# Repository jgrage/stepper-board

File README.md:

# stepper-board
Stepper motor controller board with NEMA-23 dimensions. This board was designed with KiCad. All manufacturing files are prepared for production at [JLCPCB](https://jlcpcb.com/). The surface mount components are placed on the top layer. All through-hole connectors are placed on the bottom layer. 

## Driver
The board features a socket for a Pololu [A4988 breakout board](https://www.pololu.com/product/1182). This chip can drive stepper motors with up to 2A per coil. Make sure to connect an appropriate power supply to the barrel jack.

## Controller
The firmware resides in an Arduino Nano that will plug into the 30-pin socket. Make sure to use a board with FT232RL chip so your controller will have a unique USB ID. The cheaper CH340 chips that are used on many clones all share the same ID. The controller receives serial commands and its 5V power via the Mini USB connector. 

## Limit switches
The firmware currently supports two mechanical limit switches in a normally closed configuration. Connect these to the two leftmost/rightmost pins of the 6-pin connector. The two middle pins are reserved for a mechanical reference switch, but this feature is not yet implemented in the firmware.

# Top layer

# Bottom layer

# Assembled

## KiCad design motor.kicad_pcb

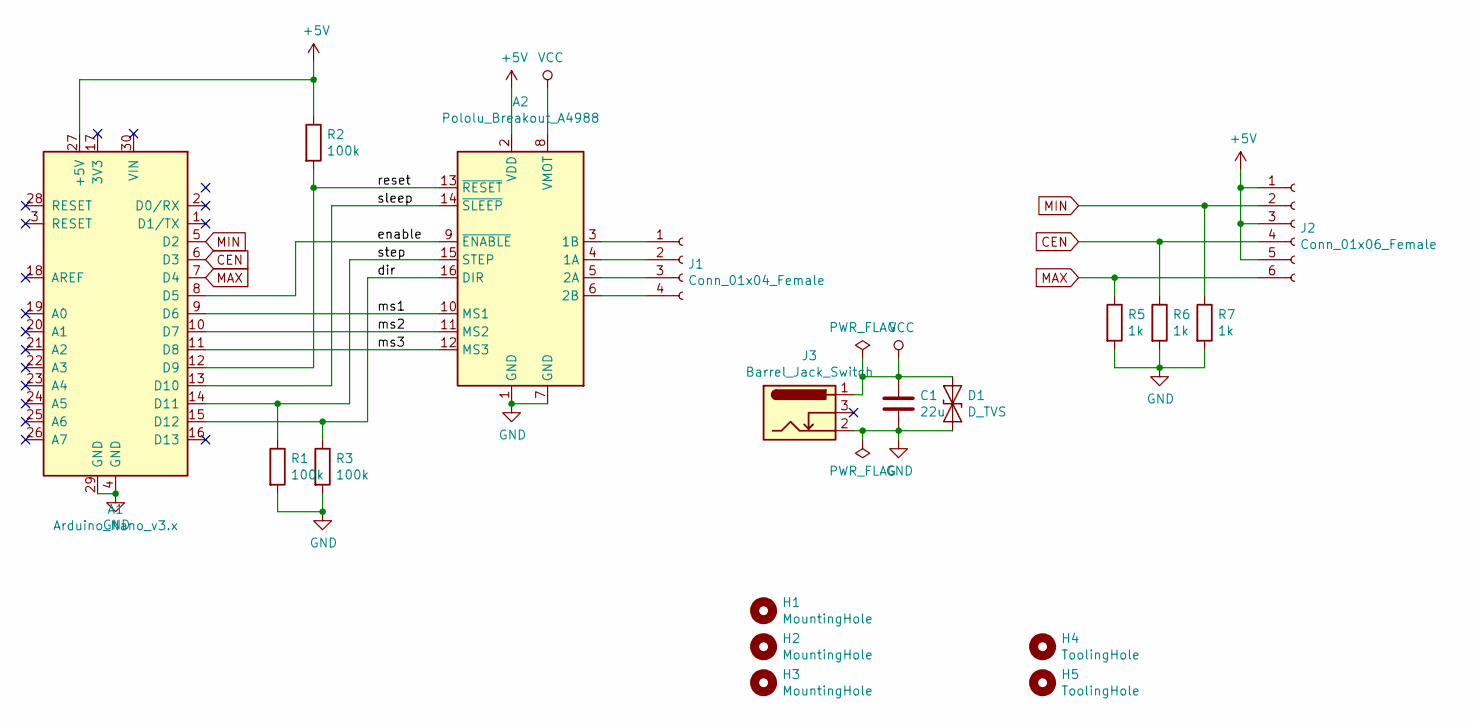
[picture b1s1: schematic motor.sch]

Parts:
A1: Arduino_Nano_v3.x; Arduino_Nano
A2: Pololu_Breakout_A4988; Pololu_Breakout-16_15.2x20.3mm
C1: 22u; C_1206_3216Metric; LCSC C13585
D1: D_TVS; D_SMB; LCSC C284012
H1, H2, H3: MountingHole; MountingHole_5mm
H4, H5: ToolingHole; Tooling_Hole_JLCPCB
J1: Conn_01x04_Female; PhoenixContact_MSTBA_2,5_4-G-5,08_1x04_P5.08mm_Horizontal
J2: Conn_01x06_Female; PhoenixContact_MC_1,5_6-G-3.5_1x06_P3.50mm_Horizontal
J3: Barrel_Jack_Switch; BarrelJack_Wuerth_6941xx301002
R1, R2, R3: 100k; R_0402_1005Metric; LCSC C25741
R5, R6, R7: 1k; R_0603_1608Metric; LCSC C25804

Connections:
+5V: A1.27 (+5V), A2.2 (VDD), J2.1, J2.3, J2.5, R2.1
/dir: A1.15 (D12), A2.16 (DIR), R3.1
/enable: A1.8 (D5), A2.9 (~ENABLE)
/ms1: A1.9 (D6), A2.10 (MS1)
/ms2: A1.10 (D7), A2.11 (MS2)
/ms3: A1.11 (D8), A2.12 (MS3)
/reset: A1.12 (D9), A2.13 (~RESET), R2.2
/sleep: A1.13 (D10), A2.14 (~SLEEP)
/step: A1.14 (D11), A2.15 (STEP), R1.1
CEN: A1.6 (D3), J2.4, R6.1
GND: A1.4 (GND), A1.29 (GND), A2.1 (GND), A2.7 (GND), C1.2, D1.2 (A2), J3.2, R1.2, R3.2, R5.2, R6.2, R7.2
MAX: A1.7 (D4), J2.6, R5.1
MIN: A1.5 (D2), J2.2, R7.1
unnamed: A2.3 (1B), J1.1
unnamed: A2.4 (1A), J1.2
unnamed: A2.5 (2A), J1.3
unnamed: A2.6 (2B), J1.4
VCC: A2.8 (VMOT), C1.1, D1.1 (A1), J3.1

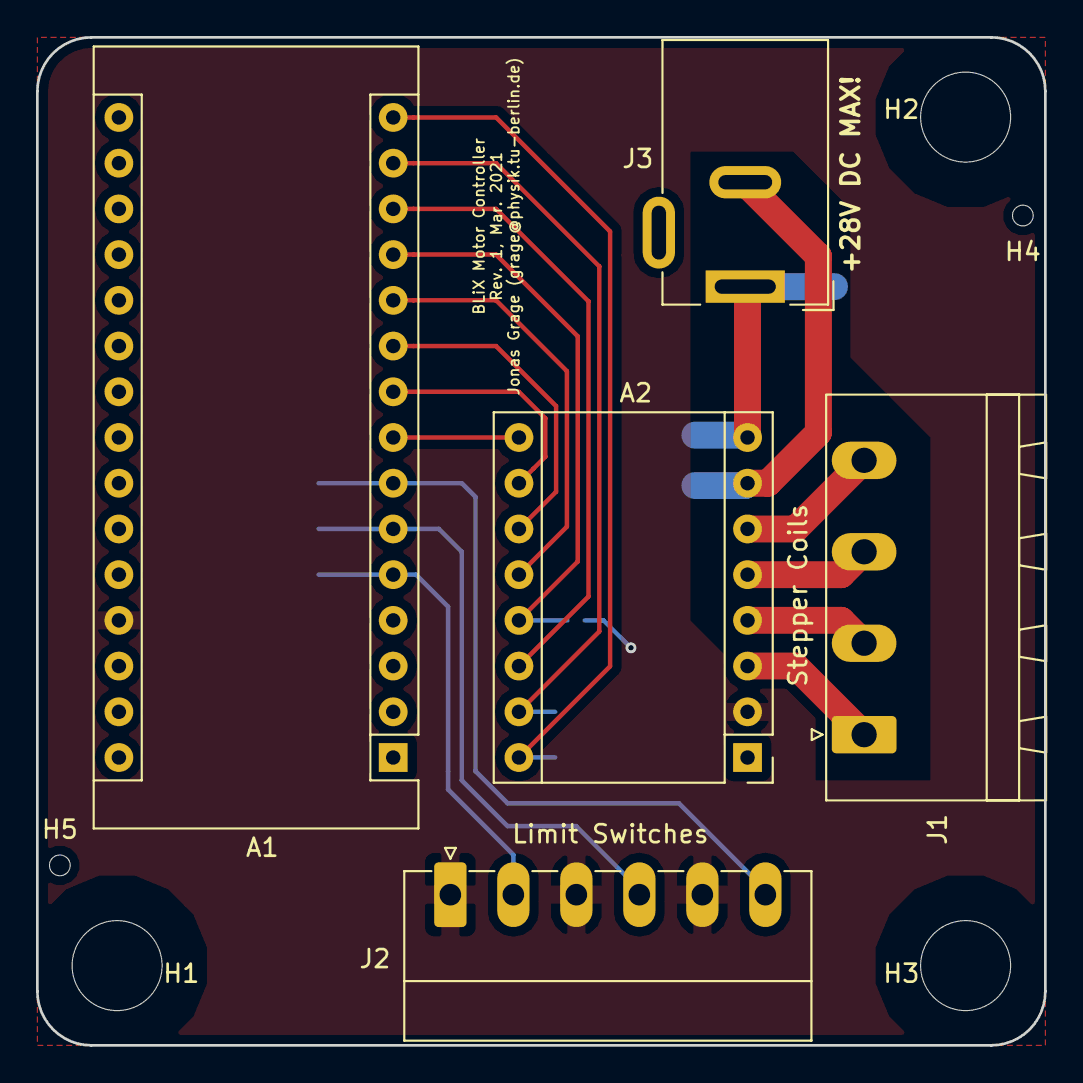
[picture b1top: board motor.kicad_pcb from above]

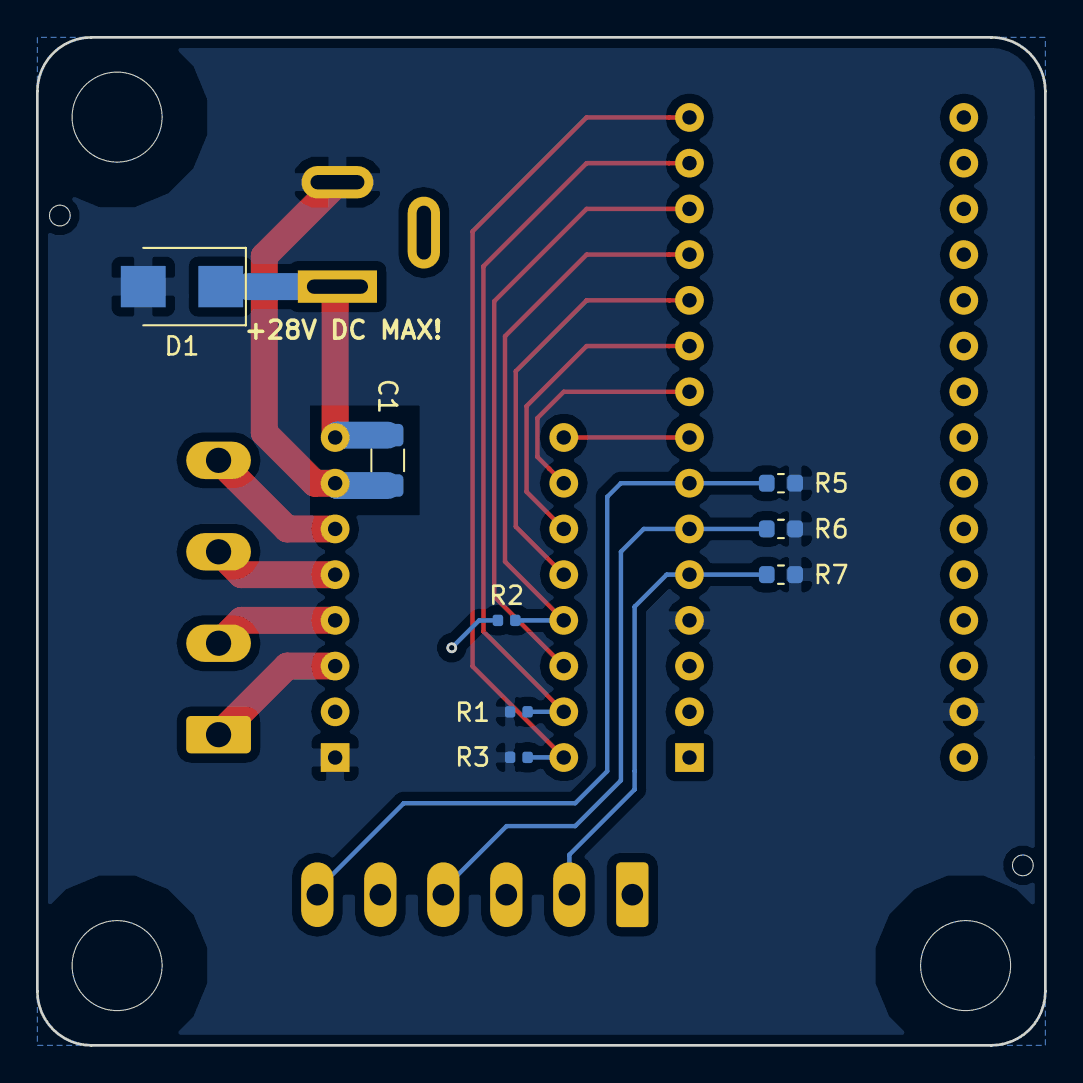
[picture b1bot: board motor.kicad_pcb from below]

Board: 2 copper layers, 56.0 x 56.0 mm, 18 parts (8 on the bottom side), 18 nets.

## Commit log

2022-04-25 license added
2023-11-03 changed to MIT license
2023-11-03 README updated
